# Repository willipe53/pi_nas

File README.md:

# pi_nas

## Bare bones Raspberry Pi NAS server

Objective was to have a simple small NAS server for local backup of my Mac using Time Machine. Setup of the Pi was based almost to the letter on [Using a Raspberry Pi for Time Machine](NASSetupArticle.pdf) by Oleg Ovechkin.

NOTE: That article, while great, is three years old as of this writing. So don't be shocked if some things behave a bit differently by the time you see this. For example, I'm pretty sure that whole section about `cd /Volumes/boot && touch ssh && cd` is unnecessary.

## Steps

1. Obtain parts. I purchased a Raspberry Pi 5, a PNY 4TB SATA drive, and a Homerun USB3.0 to SATA-III adapter. For the "hat" I used prototype board, headers, buttons, and a 0.91 Inch I2C OLED display that I had laying around.
2. Set up the Pi. Follow the Ovechkin article referenced above. I copied my `smb.conf`, `samba.service`, `hdparm.conf`, and `fstab` files into this repository just so I could easily reproduce this setup. I also captured some memorable commands from my [shell history](history.bash), but if you follow the article you shouldn't need any of that.
3. Support the Pi. You can print [NAS Spacer.stl](NAS_Spacer.stl) on a 3D printer so the Pi doesn't bounce around being suspended only by the USB interface. Or if you're not fancy you could use a blob of hot glue.
4. Enable I2C in the Interfaces section of `sudo raspiconfig`.
5. Install the [adafruit-circuitpython-ssd1306](https://docs.circuitpython.org/projects/ssd1306/en/latest/) python library so the buttons can talk to the OLED display.
6. Build the hat. It uses pins 1 through 6 on the Pi header to give you push-button status on SATA drive utilization. I didn't bother etching a circuit board for this, but I included the Eagle [nas_control_v1.brd](nas_control_v1.brd) and [nas_control_v1.sch](nas_control_v1.sch) files for documentation purposes. The signals on Pi pins 1 through 6 are `VCC`, `SDA`, `SCK`, `GP04`, `GND`, and `GP17`:

Finally, you'll need to write a python script such as [disk_status.py](disk_status.py) to listen for push buttons. Set up the script to restart every time the Pi boots by putting the following into your crontab:

```bash
@reboot /home/pi/disk_status.py &
```

In my case the button on the left causes the OLED display to cycle through some disk drive status strings:

```python
oledPrint(f"{total_tb:.2f} TB total")
oledPrint(f"{used_tb:.2f} TB used")
oledPrint(f"{free_tb:.2f} TB free")
oledPrint(f"{percent_used:.1f}% used")
```

and the button on the right resets the Pi:

```python
oledPrint("Rebooting...")
os.system("sudo reboot")
```

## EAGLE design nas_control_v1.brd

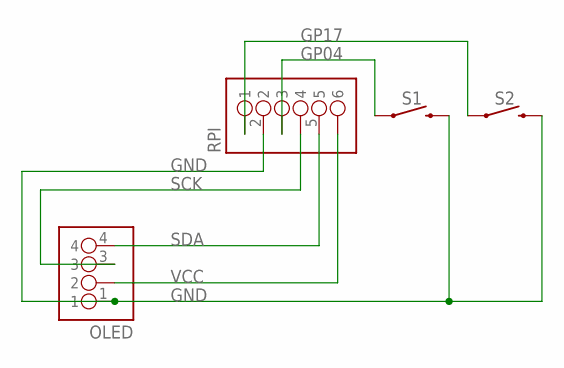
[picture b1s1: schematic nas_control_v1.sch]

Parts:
OLED: PINHD-1X04_1X04M; 1X04
RPI: PINHD-1X06_1X06M; 1X06
S1, S2: MOMENTARY-SWITCH-SPST-PTH-6.0MM; TACTILE_SWITCH_PTH_6.0MM

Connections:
GND: OLED.1, RPI.2, S1.3 (2), S2.3 (2)
GP04: RPI.3, S1.1
GP17: RPI.1, S2.1
SCK: OLED.3, RPI.4
SDA: OLED.4, RPI.5
VCC: OLED.2, RPI.6

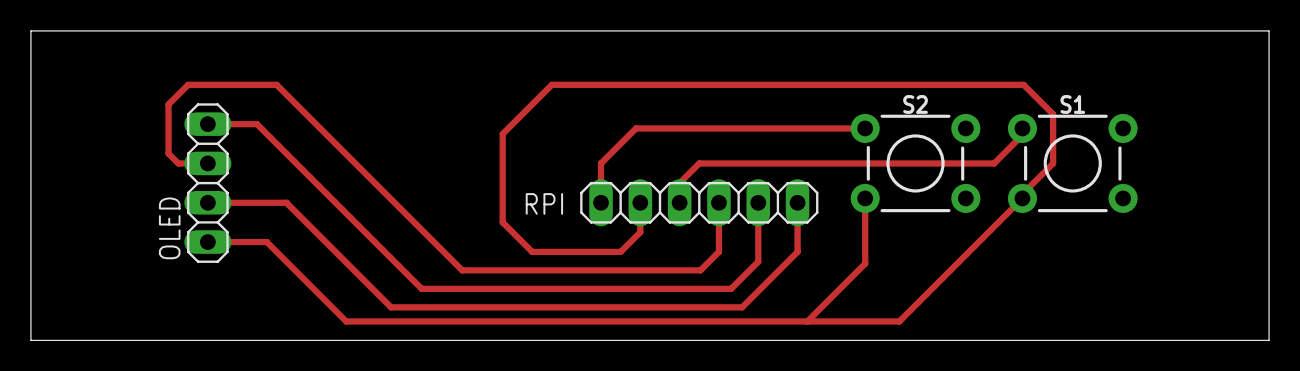
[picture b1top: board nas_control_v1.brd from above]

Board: 2 copper layers, 80.0 x 20.0 mm, 4 parts (0 on the bottom side), 6 nets.

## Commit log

2025-05-26 Documentation updated

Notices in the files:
parts and their libraries:
SparkFun-Switches: Licensing: Creative Commons ShareAlike 4.0 International - https://creativecommons.org/licenses/by-sa/4.0
